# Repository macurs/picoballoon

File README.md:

- hw/ : PCB project made using KiCad 7.0
- hw/bom/ : interactive bill of materials
- hw/plots/ : PCB export to PDF

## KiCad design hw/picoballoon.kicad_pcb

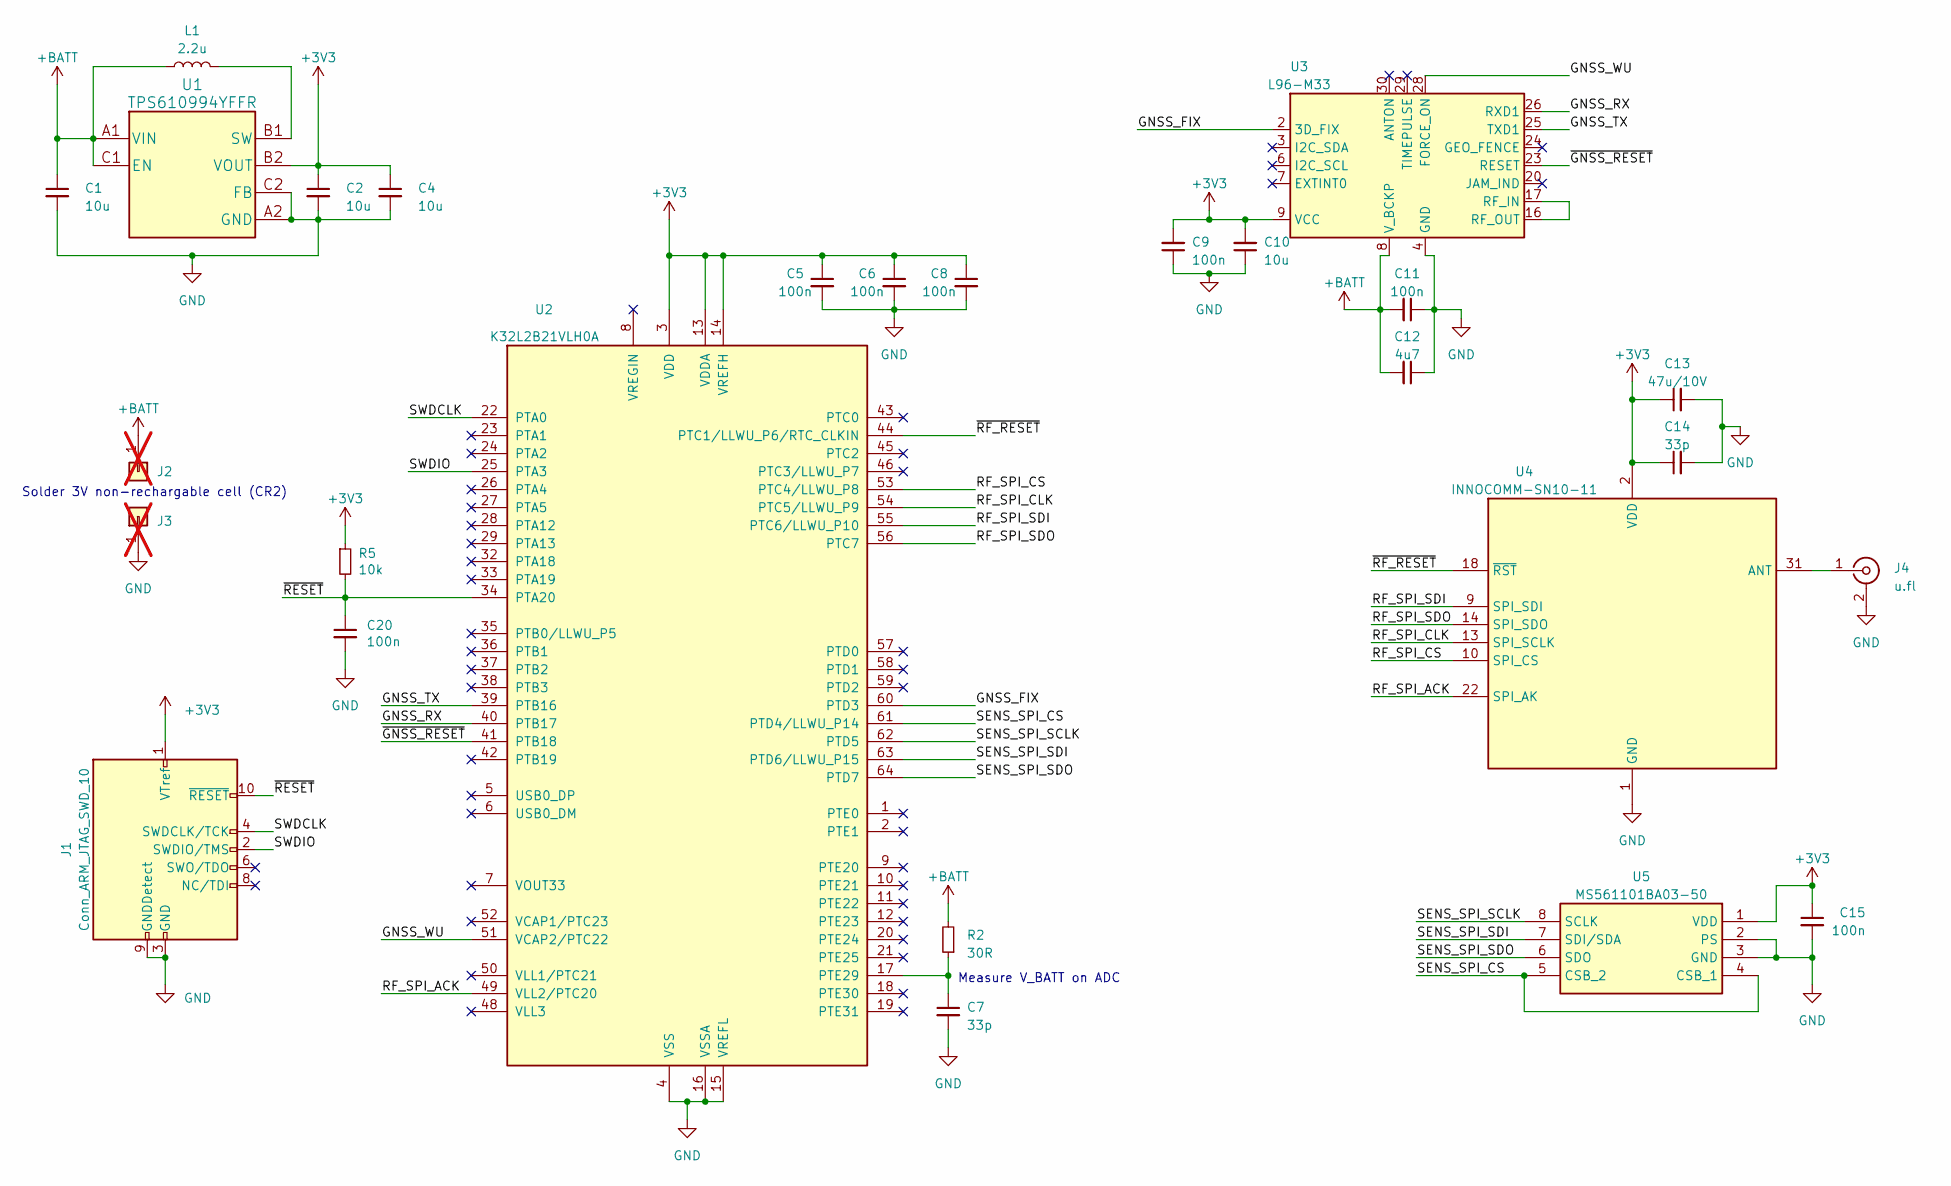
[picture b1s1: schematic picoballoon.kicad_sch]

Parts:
C1, C2, C4, C10: 10u; C_0603_1608Metric; Manufacturer_Part_Number JMK107ABJ106MA-T
C5, C6, C8, C9, C11, C15, C20: 100n; C_0603_1608Metric; Manufacturer_Part_Number CL10B104KO8NNWC
C7, C14: 33p; C_0603_1608Metric; Manufacturer_Part_Number CL10C330JC81PNC
C12: 4u7; C_0603_1608Metric; Manufacturer_Part_Number CL10A475KQ8NNNC; Mouser Part Number CL10A475KQ8NNNC
C13: 47u/10V; C_0603_1608Metric; Manufacturer_Part_Number GRM188R60G476ME15J; Mouser Part Number GRM188R60G476ME15J
J1: Conn_ARM_JTAG_SWD_10; PinHeader_2x05_P1.27mm_Vertical; Manufacturer_Part_Number M50-3500542
J2, J3: PinHeader_1x01_P2.54mm_Vertical; Manufacturer_Part_Number dnp; not fitted
J4: u.fl; U.FL_Hirose_U.FL-R-SMT-1_Vertical; Manufacturer_Part_Number U.FL-R-SMT-1(10)
L1: 2.2u; L_0603_1608Metric; Manufacturer_Part_Number LQM18PN2R2MGHD
R2: 30R; R_0603_1608Metric; Manufacturer_Part_Number RC0603FR-0730RL; Mouser Part Number RC0603FR-0730RL
R5: 10k; R_0603_1608Metric; Manufacturer_Part_Number RC0603JR-0710KP
U1: TPS610994YFFR; Manufacturer_Part_Number TPS610994YFFR
U2: K32L2B21VLH0A; LQFP-64_10x10mm_P0.5mm; Manufacturer_Part_Number K32L2B21VLH0A
U3: L96-M33; Quectel_L96-M33; Manufacturer_Part_Number L96-M33
U4: INNOCOMM-SN10-11; InnoCommSN10-11; Manufacturer_Part_Number INNOCOMM-SN10-11
U5: MS561101BA03-50; Manufacturer_Part_Number MS561101BA03-50; Mouser Part Number 824-MS561101BA03-50

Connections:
+3V3: C2.1, C4.1, C5.1, C6.1, C8.1, C9.2, C10.2, C13.1, C14.1, C15.1, J1.1 (VTref), U1.B2 (VOUT), U2.3 (VDD), U2.13 (VDDA), U2.14 (VREFH), U2.30 (VDD), U3.9 (VCC), U4.2 (VDD), U5.1 (VDD); also elsewhere on the board
+BATT: C1.1, C11.2, C12.2, J2.1, L1.1, R2.2, U1.A1 (VIN), U1.C1 (EN), U3.8 (V_BCKP)
/GNSS_FIX: U2.60 (PTD3), U3.2 (3D_FIX)
/GNSS_RX: U2.40 (PTB17), U3.26 (RXD1)
/GNSS_TX: U2.39 (PTB16), U3.25 (TXD1)
/GNSS_WU: U2.51 (VCAP2/PTC22), U3.28 (FORCE_ON)
/RF_SPI_ACK: U2.49 (VLL2/PTC20), U4.22 (SPI_AK)
/RF_SPI_CLK: U2.54 (PTC5/LLWU_P9), U4.13 (SPI_SCLK)
/RF_SPI_CS: U2.53 (PTC4/LLWU_P8), U4.10 (SPI_CS)
/RF_SPI_SDI: U2.55 (PTC6/LLWU_P10), U4.9 (SPI_SDI)
/RF_SPI_SDO: U2.56 (PTC7), U4.14 (SPI_SDO)
/SENS_SPI_CS: U2.61 (PTD4/LLWU_P14), U5.4 (CSB_1), U5.5 (CSB_2)
/SENS_SPI_SCLK: U2.62 (PTD5), U5.8 (SCLK)
/SENS_SPI_SDI: U2.63 (PTD6/LLWU_P15), U5.7 (SDI/SDA)
/SENS_SPI_SDO: U2.64 (PTD7), U5.6 (SDO)
/SWDCLK: J1.4 (SWDCLK/TCK), U2.22 (PTA0)
/SWDIO: J1.2 (SWDIO/TMS), U2.25 (PTA3)
/~GNSS_RESET: U2.41 (PTB18), U3.23 (RESET)
/~RESET: J1.10 (~RESET), U2.34 (PTA20); also elsewhere on the board
/~RF_RESET: U2.44 (PTC1/LLWU_P6/RTC_CLKIN), U4.18 (~RST)
GND: C1.2, C2.2, C4.2, C5.2, C6.2, C7.2, C8.2, C9.1, C10.1, C11.1, C12.1, C13.2, C14.2, C15.2, J1.3 (GND), J1.5 (GND), J1.9 (GNDDetect), J3.1, J4.2 (Ext), U1.A2 (GND), U1.C2 (FB), U2.4 (VSS), U2.15 (VREFL), U2.16 (VSSA), U2.31 (VSS), U2.47 (VSS), U3.4 (GND), U3.5 (GND), U3.10 (GND), U3.11 (GND), U3.12 (GND), U3.13 (GND), U3.14 (GND), U3.15 (GND), U3.18 (GND), U3.19 (GND), U3.21 (GND), U3.22 (GND), U3.27 (GND), U3.31 (GND), U4.1 (GND), U4.3 (GND), U4.4 (GND), U4.5 (GND), U4.6 (GND), U4.7 (GND), U4.8 (GND), U4.11 (GND), U4.12 (GND), U4.21 (GND), U4.27 (GND), U4.30 (GND), U4.32 (GND), U5.2 (PS), U5.3 (GND); also elsewhere on the board
unnamed: J4.1 (In), U4.31 (ANT)
unnamed: L1.2, U1.B1 (SW)
unnamed: C7.1, R2.1, U2.17 (PTE29)
unnamed: U3.16 (RF_OUT), U3.17 (RF_IN)

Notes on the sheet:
Solder 3V non-rechargable cell (CR2)
Measure V_BATT on ADC

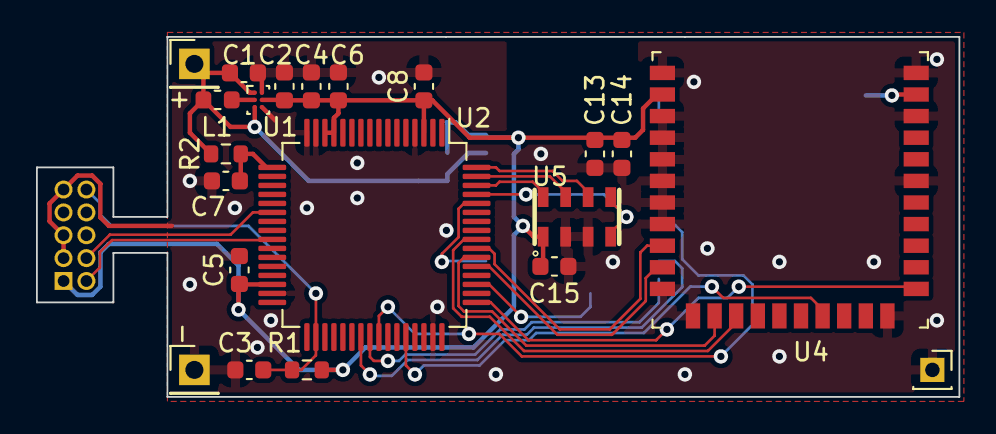
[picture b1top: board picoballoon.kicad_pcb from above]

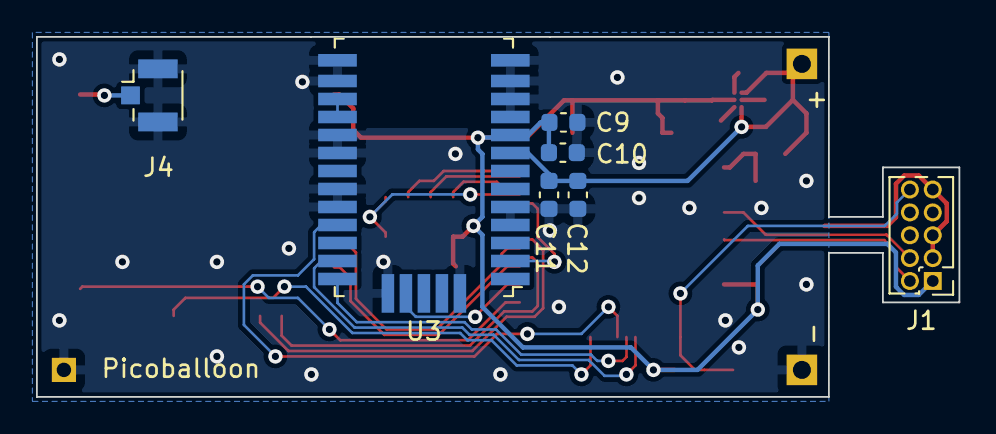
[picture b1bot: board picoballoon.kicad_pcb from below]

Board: 2 copper layers, 51.2 x 20.0 mm, 28 parts (7 on the bottom side), 25 nets.

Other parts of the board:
C3: 100n; C_0603_1608Metric
J0: PinSocket_1x01_P2.00mm_Vertical
R1: 10k; R_0603_1608Metric

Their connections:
+3V3: R1.1; also elsewhere on the board
/~RESET: C3.1, R1.2; also elsewhere on the board
GND: C3.2, J0.1; also elsewhere on the board

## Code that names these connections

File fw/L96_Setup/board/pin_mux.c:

/***********************************************************************************************************************
 * This file was generated by the MCUXpresso Config Tools. Any manual edits made to this file
 * will be overwritten if the respective MCUXpresso Config Tools is used to update this file.
 **********************************************************************************************************************/

/* clang-format off */
/*
 * TEXT BELOW IS USED AS SETTING FOR TOOLS *************************************
!!GlobalInfo
product: Pins v13.1
processor: K32L2B21xxxxA
package_id: K32L2B21VLH0A
mcu_data: ksdk2_0
processor_version: 13.0.1
pin_labels:
- {pin_num: '41', pin_signal: LCD_P14/PTB18/TPM2_CH0, label: GNSS_RESET, identifier: GNSS_RESET}
- {pin_num: '60', pin_signal: LCD_P43/PTD3/SPI0_MISO/UART2_TX/TPM0_CH3/SPI0_MOSI/FXIO0_D3, label: GNSS_FIX, identifier: GNSS_FIX}
- {pin_num: '51', pin_signal: VCAP2/LCD_P6/PTC22, label: GNSS_WU, identifier: GNSS_WU}
- {pin_num: '40', pin_signal: LCD_P13/PTB17/SPI1_MISO/LPUART0_TX/TPM_CLKIN1/SPI1_MOSI, label: GNSS_TX, identifier: GNSS_TX}
- {pin_num: '39', pin_signal: LCD_P12/PTB16/SPI1_MOSI/LPUART0_RX/TPM_CLKIN0/SPI1_MISO, label: GNSS_RX, identifier: GNSS_RX}
 * BE CAREFUL MODIFYING THIS COMMENT - IT IS YAML SETTINGS FOR TOOLS ***********
 */
/* clang-format on */

#include "fsl_common.h"
#include "fsl_port.h"
#include "fsl_gpio.h"
#include "pin_mux.h"

/* FUNCTION ************************************************************************************************************
 *
 * Function Name : BOARD_InitBootPins
 * Description   : Calls initialization functions.
 *
 * END ****************************************************************************************************************/
void BOARD_InitBootPins(void)
{
    BOARD_InitPins();
}

/* clang-format off */
/*
 * TEXT BELOW IS USED AS SETTING FOR TOOLS *************************************
BOARD_InitPins:
- options: {callFromInitBoot: 'true', coreID: core0, enableClock: 'true'}
- pin_list:
  - {pin_num: '40', peripheral: LPUART0, signal: TX, pin_signal: LCD_P13/PTB17/SPI1_MISO/LPUART0_TX/TPM_CLKIN1/SPI1_MOSI, direction: OUTPUT}
  - {pin_num: '39', peripheral: LPUART0, signal: RX, pin_signal: LCD_P12/PTB16/SPI1_MOSI/LPUART0_RX/TPM_CLKIN0/SPI1_MISO}
  - {pin_num: '41', peripheral: GPIOB, signal: 'GPIO, 18', pin_signal: LCD_P14/PTB18/TPM2_CH0, direction: OUTPUT, gpio_init_state: 'true', pull_enable: enable}
  - {pin_num: '60', peripheral: GPIOD, signal: 'GPIO, 3', pin_signal: LCD_P43/PTD3/SPI0_MISO/UART2_TX/TPM0_CH3/SPI0_MOSI/FXIO0_D3, direction: INPUT}
  - {pin_num: '51', peripheral: GPIOC, signal: 'GPIO, 22', pin_signal: VCAP2/LCD_P6/PTC22, direction: OUTPUT}
 * BE CAREFUL MODIFYING THIS COMMENT - IT IS YAML SETTINGS FOR TOOLS ***********
 */
/* clang-format on */

/* FUNCTION ************************************************************************************************************
 *
 * Function Name : BOARD_InitPins
 * Description   : Configures pin routing and optionally pin electrical features.
 *
 * END ****************************************************************************************************************/
void BOARD_InitPins(void)
{
    /* Port B Clock Gate Control: Clock enabled */
    CLOCK_EnableClock(kCLOCK_PortB);
    /* Port C Clock Gate Control: Clock enabled */
    CLOCK_EnableClock(kCLOCK_PortC);
    /* Port D Clock Gate Control: Clock enabled */
    CLOCK_EnableClock(kCLOCK_PortD);

    gpio_pin_config_t GNSS_RESET_config = {
        .pinDirection = kGPIO_DigitalOutput,
        .outputLogic = 1U
    };
    /* Initialize GPIO functionality on pin PTB18 (pin 41)  */
    GPIO_PinInit(BOARD_INITPINS_GNSS_RESET_GPIO, BOARD_INITPINS_GNSS_RESET_PIN, &GNSS_RESET_config);

    gpio_pin_config_t GNSS_WU_config = {
        .pinDirection = kGPIO_DigitalOutput,
        .outputLogic = 0U
    };
    /* Initialize GPIO functionality on pin PTC22 (pin 51)  */
    GPIO_PinInit(BOARD_INITPINS_GNSS_WU_GPIO, BOARD_INITPINS_GNSS_WU_PIN, &GNSS_WU_config);

    gpio_pin_config_t GNSS_FIX_config = {
        .pinDirection = kGPIO_DigitalInput,
        .outputLogic = 0U
    };
    /* Initialize GPIO functionality on pin PTD3 (pin 60)  */
    GPIO_PinInit(BOARD_INITPINS_GNSS_FIX_GPIO, BOARD_INITPINS_GNSS_FIX_PIN, &GNSS_FIX_config);

    /* PORTB16 (pin 39) is configured as LPUART0_RX */
    PORT_SetPinMux(BOARD_INITPINS_GNSS_RX_PORT, BOARD_INITPINS_GNSS_RX_PIN, kPORT_MuxAlt3);

    /* PORTB17 (pin 40) is configured as LPUART0_TX */
    PORT_SetPinMux(BOARD_INITPINS_GNSS_TX_PORT, BOARD_INITPINS_GNSS_TX_PIN, kPORT_MuxAlt3);

    /* PORTB18 (pin 41) is configured as PTB18 */
    PORT_SetPinMux(BOARD_INITPINS_GNSS_RESET_PORT, BOARD_INITPINS_GNSS_RESET_PIN, kPORT_MuxAsGpio);

    PORTB->PCR[18] = ((PORTB->PCR[18] &
                       /* Mask bits to zero which are setting */
                       (~(PORT_PCR_PE_MASK | PORT_PCR_ISF_MASK)))

                      /* Pull Enable: Internal pullup or pulldown resistor is enabled on the corresponding pin. */
                      | (uint32_t)(PORT_PCR_PE_MASK));

    /* PORTC22 (pin 51) is configured as PTC22 */
    PORT_SetPinMux(BOARD_INITPINS_GNSS_WU_PORT, BOARD_INITPINS_GNSS_WU_PIN, kPORT_MuxAsGpio);

    /* PORTD3 (pin 60) is configured as PTD3 */
    PORT_SetPinMux(BOARD_INITPINS_GNSS_FIX_PORT, BOARD_INITPINS_GNSS_FIX_PIN, kPORT_MuxAsGpio);

    SIM->SOPT5 = ((SIM->SOPT5 &
                   /* Mask bits to zero which are setting */
                   (~(SIM_SOPT5_LPUART0TXSRC_MASK | SIM_SOPT5_LPUART0RXSRC_MASK)))

                  /* LPUART0 Transmit Data Source Select: LPUART0_TX pin. */
                  | SIM_SOPT5_LPUART0TXSRC(SOPT5_LPUART0TXSRC_LPUART_TX)

                  /* LPUART0 Receive Data Source Select: LPUART_RX pin. */
                  | SIM_SOPT5_LPUART0RXSRC(SOPT5_LPUART0RXSRC_LPUART_RX));
}
/***********************************************************************************************************************
 * EOF
 **********************************************************************************************************************/

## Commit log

2023-03-24 init commit
2023-03-27 part #s
2023-03-28 exports
2023-03-29 ant trace width
2023-03-29 gnss_uart
2023-03-29 pcb cleanup
2023-03-29 update DRC rule
2023-03-30 tracks cleanup
2023-03-30 change gps reset pin
    cleanup pcb tracks
2023-04-12 fix swd footprint
2023-04-19 bom with part #s
2023-04-19 parts datasheet links in schematic
2023-05-31 add fw
